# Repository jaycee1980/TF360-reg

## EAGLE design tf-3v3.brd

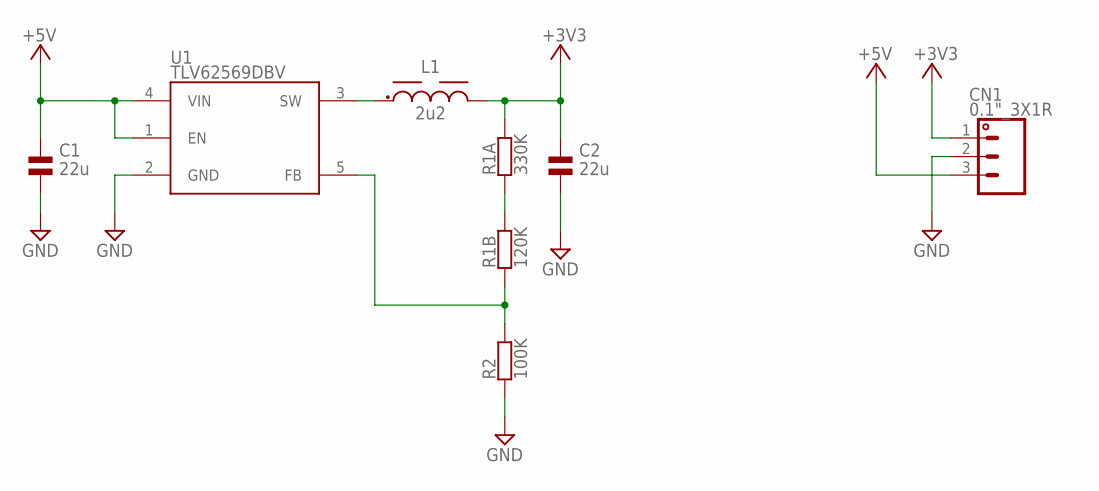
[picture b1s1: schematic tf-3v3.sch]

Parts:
C1, C2: 22u; 0805; LCSC_PART C45783
CN1: 0.1"_3X1R; 0.1"_3X1-ROUND
L1: 2u2; ANR6028; LCSC_PART C7427146
R1A: 330K; 0603; LCSC_PART C23137
R1B: 120K; 0603; LCSC_PART C25808
R2: 100K; 0603; LCSC_PART C25803
U1: TLV62569DBV; SOT23-5; JLC_ROTATION -90

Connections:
+3V3: C2.1, CN1.1, L1.P$2 (2), R1A.2
+5V: C1.1, CN1.3, U1.1 (EN), U1.4 (VIN)
FB: R1B.1, R2.2, U1.5 (FB)
GND: C1.2, C2.2, CN1.2, R2.1, U1.2 (GND)
unnamed: R1A.1, R1B.2
SW: L1.P$1 (1), U1.3 (SW)

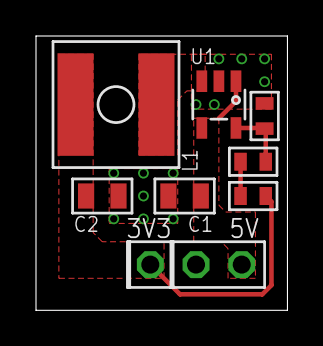
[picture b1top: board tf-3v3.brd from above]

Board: 2 copper layers, 14.0 x 15.2 mm, 8 parts (0 on the bottom side), 6 nets.

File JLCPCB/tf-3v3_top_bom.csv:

Comment,Designator,Footprint,LCSC Part #
2u2,L1,ANR6028,C7427146
22u,C1,0805,C45783
22u,C2,0805,C45783
100K,R2,0603,C25803
120K,R1B,0603,C25808
330K,R1A,0603,C23137
TLV62569DBV,U1,SOT23-5,C141836
